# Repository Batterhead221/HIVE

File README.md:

# HIVE

ESP32-C6 gateway board for receiving GRUNT outlet/circuit heartbeat packets.

HIVE is the central receiver in the HIVE + GRUNT monitoring system. It listens for ESP-NOW heartbeat packets from one or more GRUNT sender nodes and reports whether each monitored outlet/circuit is ON, OFF, or waiting for first heartbeat.

## Project Status

Prototype hardware designed. ESP-NOW proof-of-concept tested with an ESP32-C6 gateway and XIAO ESP32-S3 sender node.

## System Role

```text
GRUNT sender node
    ↓ ESP-NOW heartbeat
HIVE gateway board
    ↓ USB serial
Computer / future dashboard
```

## Hardware

Main parts:

- ESP32-C6-WROOM-1-N8 module
- USB-C power and data
- AP2112K-3.3 voltage regulator
- USBLC6-2P6 USB ESD protection
- BOOT and RESET buttons
- RGB status LED
- Power LED
- UART debug pads
- 4-layer PCB with internal GND plane

## Power

HIVE is powered from USB-C VBUS.

```text
USB-C VBUS → fuse/protection → +5V
+5V → AP2112K-3.3 → +3.3V
+3.3V → ESP32-C6-WROOM-1-N8
```

## USB-C

USB-C is used for both power and native ESP32-C6 USB data.

```text
USB D- → ESP32-C6 GPIO12 / USB_D-
USB D+ → ESP32-C6 GPIO13 / USB_D+
CC1 → 5.1k → GND
CC2 → 5.1k → GND
USB shield → GND
```

## Firmware Behavior

HIVE receives heartbeat packets from GRUNT nodes over ESP-NOW.

Each packet contains:

```cpp
typedef struct {
  char nodeId[16];
  uint32_t counter;
  uint32_t uptimeMs;
} HeartbeatPacket;
```

HIVE tracks the last-seen time for each node.

```text
recent heartbeat → node is ON
timeout expired  → node is OFF / missing
never seen       → node is UNKNOWN
```

## PCB Notes

Recommended layer strategy:

```text
T.SIGNAL → components, USB, local signals
GND      → solid internal GND plane
PWR      → +3.3V pour / power routing
B.SIGNAL → GND pour and slow signals
```

Antenna keepout must block copper on all layers:

- No tracks
- No vias
- No pads
- No zone fills
- No components

## Safety Note

HIVE is a low-voltage USB-powered gateway. It does not connect directly to mains voltage.

## Known Notes

- HIVE is the receiver/gateway board.
- GRUNT is the sender/outlet node.
- ESP-NOW devices must be on the same Wi-Fi channel.
- The ESP32-C6 module antenna keepout is critical for reliable wireless performance.
- UART debug pads are included as a backup even though native USB is used.

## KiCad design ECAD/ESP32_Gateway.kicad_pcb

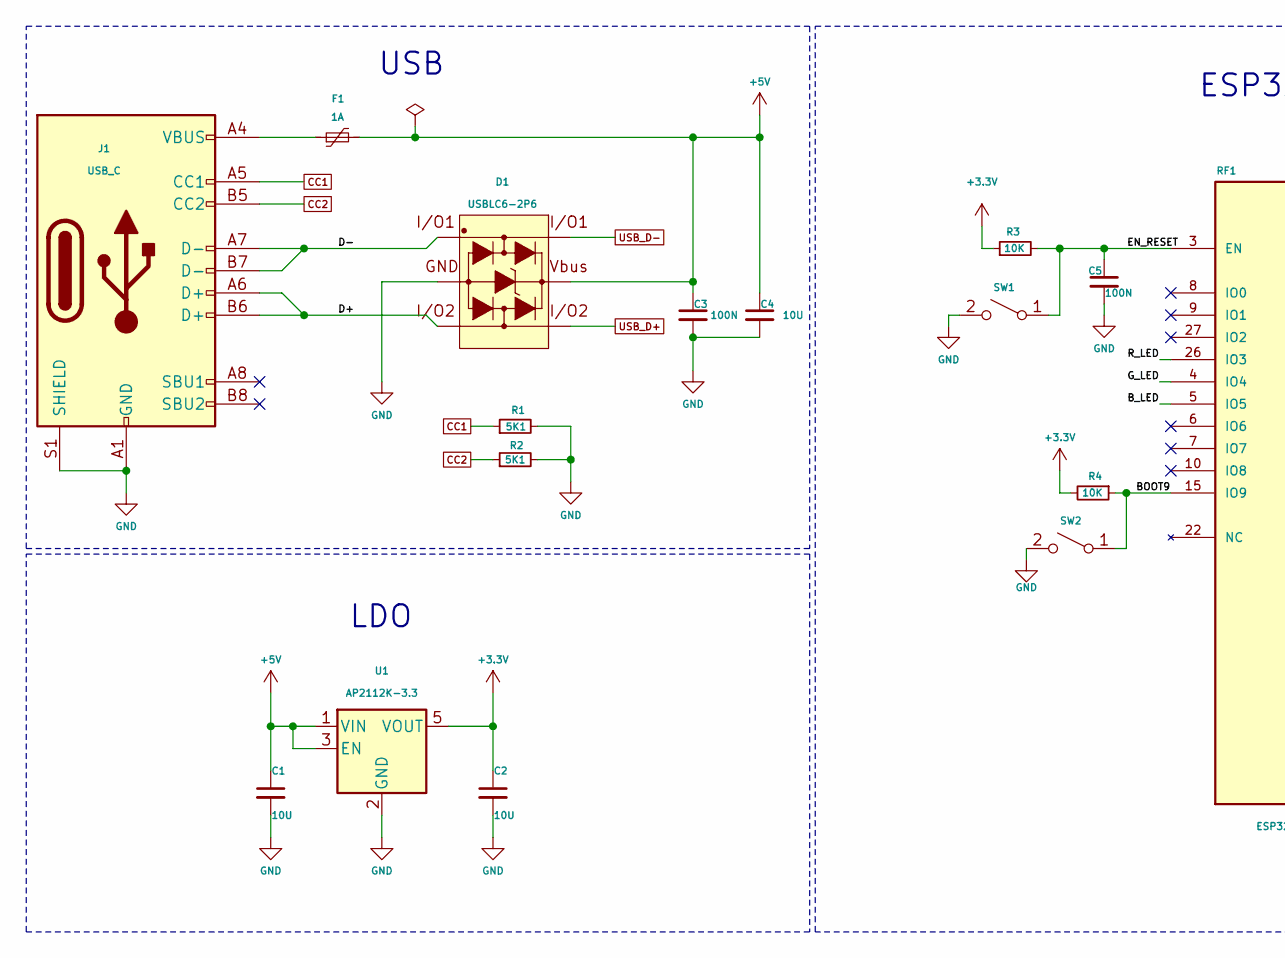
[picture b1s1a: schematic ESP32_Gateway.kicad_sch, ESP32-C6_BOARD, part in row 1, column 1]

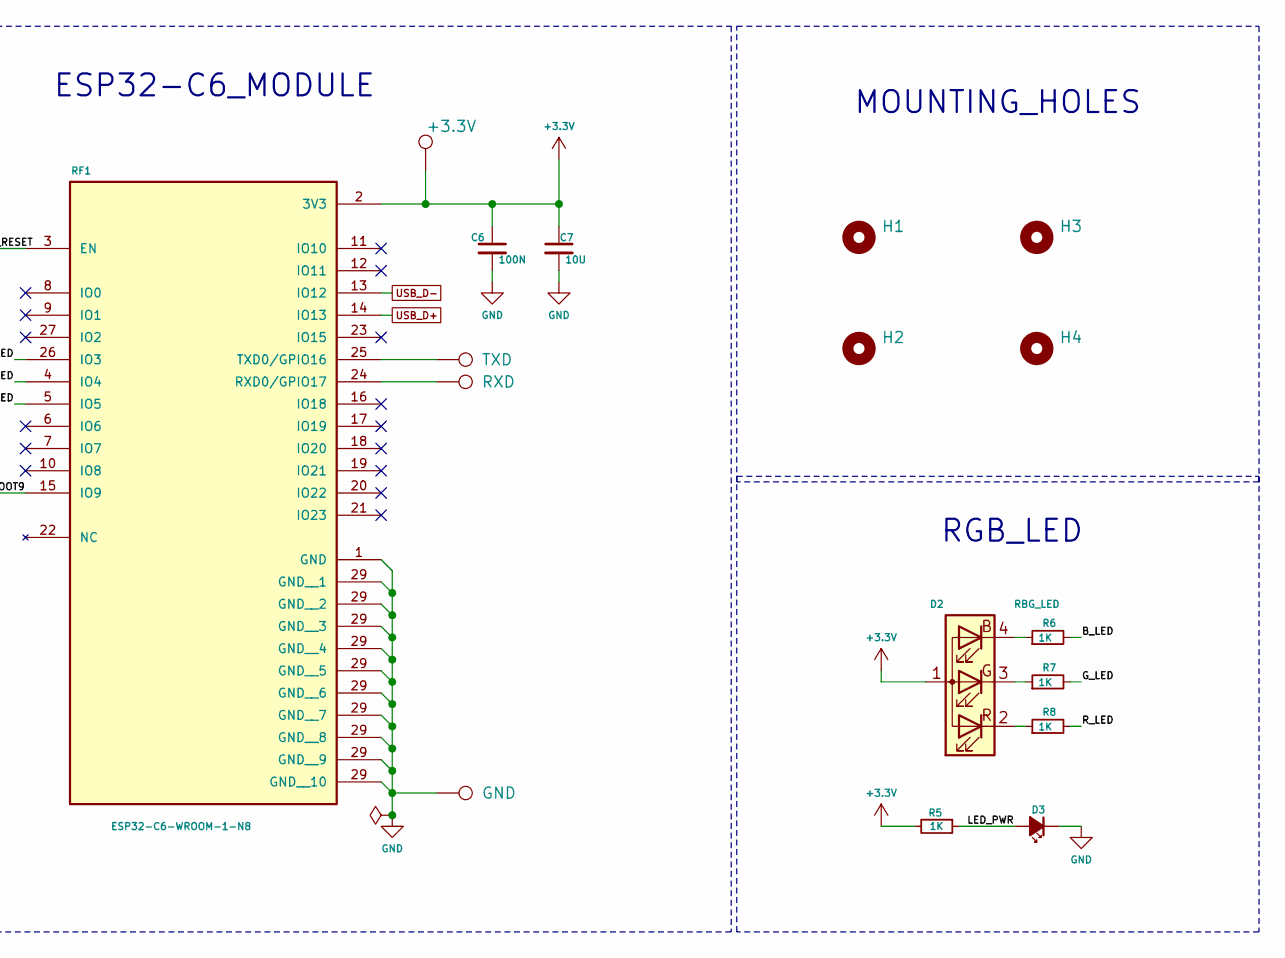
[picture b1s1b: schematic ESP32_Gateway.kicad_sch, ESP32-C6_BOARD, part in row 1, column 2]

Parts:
C1, C2, C4, C7: 10U; C_0805_2012Metric
C3, C5, C6: 100N; C_0603_1608Metric
D1: USBLC6-2P6; SOT-666
D2: RBG_LED; LED_Cree-PLCC4_3.2x2.8mm_CCW
D3: GREEN; LED_0603_1608Metric
F1: 1A; Fuse_1206_3216Metric
H1, H2, H3, H4: MountingHole; MountingHole_2.2mm_M2
J1: USB_C; USB_C_Receptacle_HRO_TYPE-C-31-M-12
R1, R2: 5K1; R_0603
R3, R4: 10K; R_0603
R5, R6, R7, R8: 1K; R_0603
RF1: ESP32-C6-WROOM-1-N8; XCVR_ESP32-C6-WROOM-1-N8; PARTREV 1.0
SW1: RESET; SW_SPST_B3U-1000P
SW2: BOOT; SW_SPST_B3U-1000P
TP1: TXD; TestPoint_THTPad_D1.5mm_Drill0.7mm
TP2: RXD; TestPoint_THTPad_D1.5mm_Drill0.7mm
TP3: GND; TestPoint_THTPad_D1.5mm_Drill0.7mm
TP4: +3.3V; TestPoint_THTPad_D1.5mm_Drill0.7mm
U1: AP2112K-3.3; SOT-23-5

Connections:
+3.3V: C2.1, C6.1, C7.1, D2.1 (A), R3.1, R4.2, R5.2, RF1.2 (3V3), TP4.1 (1_1), U1.5 (VOUT)
+5V: C1.1, C3.1, C4.1, D1.5 (Vbus), F1.2, U1.1 (VIN), U1.3 (EN)
/BOOT9: R4.1, RF1.15 (IO9), SW2.1 (A)
/B_LED: R6.2, RF1.5 (IO5)
/D+: D1.3 (I/O2), J1.A6 (D+), J1.B6 (D+)
/D-: D1.1 (I/O1), J1.A7 (D-), J1.B7 (D-)
/EN_RESET: C5.1, R3.2, RF1.3 (EN), SW1.1 (A)
/G_LED: R7.2, RF1.4 (IO4)
/LED_PWR: D3.2 (A), R5.1
/R_LED: R8.2, RF1.26 (IO3)
CC1: J1.A5 (CC1), R1.1
CC2: J1.B5 (CC2), R2.1
GND: C1.2, C2.2, C3.2, C4.2, C5.2, C6.2, C7.2, D1.2 (GND), D3.1 (K), J1.A1 (GND), J1.A12 (GND), J1.B1 (GND), J1.B12 (GND), J1.S1 (SHIELD), R1.2, R2.2, RF1.1 (GND), RF1.29 (GND__1), SW1.2 (B), SW2.2 (B), TP3.1 (1_1), U1.2 (GND)
unnamed: D2.4 (BK), R6.1
unnamed: D2.3 (GK), R7.1
unnamed: D2.2 (RK), R8.1
unnamed: F1.1, J1.A4 (VBUS), J1.A9 (VBUS), J1.B4 (VBUS), J1.B9 (VBUS)
unnamed: RF1.24 (RXD0/GPIO17), TP2.1 (1_1)
unnamed: RF1.25 (TXD0/GPIO16), TP1.1 (1_1)
USB_D+: D1.4 (I/O2+), RF1.14 (IO13)
USB_D-: D1.6 (I/O1+), RF1.13 (IO12)

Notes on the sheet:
LDO
MOUNTING_HOLES
RGB_LED
ESP32-C6_MODULE
USB

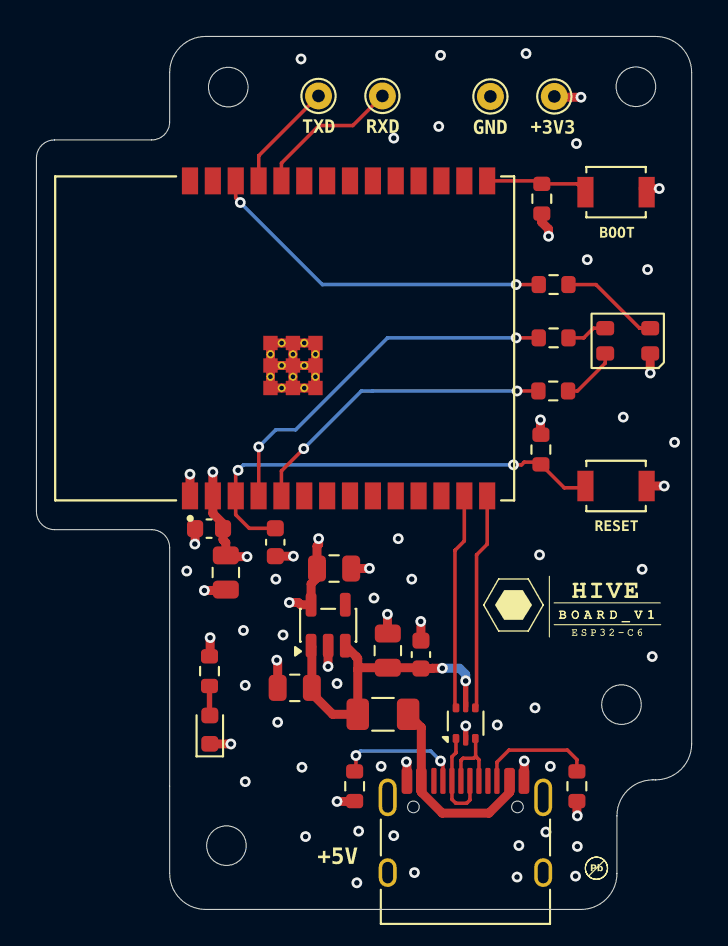
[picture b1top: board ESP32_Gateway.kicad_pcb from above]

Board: 4 copper layers, 36.4 x 48.5 mm, 32 parts (0 on the bottom side), 21 nets.

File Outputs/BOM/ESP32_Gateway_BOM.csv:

"Id";"Designator";"Footprint";"Quantity";"Designation";"Supplier and ref";
1;"C1, C2, C4, C7";"C_0805_2012Metric";4;"10U";;;
2;"C3, C5, C6";"C_0603_1608Metric";3;"100N";;;
3;"D1";"SOT-666";1;"USBLC6-2P6";;;
4;"D2";"LED_Cree-PLCC4_3.2x2.8mm_CCW";1;"RBG_LED";;;
5;"D3";"LED_0603_1608Metric";1;"GREEN";;;
6;"F1";"Fuse_1206_3216Metric";1;"1A";;;
7;"J1";"USB_C_Receptacle_HRO_TYPE-C-31-M-12";1;"USB_C";;;
8;"R1, R2";"R_0603";2;"5K1";;;
9;"R3, R4";"R_0603";2;"10K";;;
10;"R5, R6, R7, R8";"R_0603";4;"1K";;;
11;"RF1";"XCVR_ESP32-C6-WROOM-1-N8";1;"ESP32-C6-WROOM-1-N8";;;
12;"SW1";"SW_SPST_B3U-1000P";1;"RESET";;;
13;"SW2";"SW_SPST_B3U-1000P";1;"BOOT";;;
14;"TP1";"TestPoint_THTPad_D1.5mm_Drill0.7mm";1;"TXD";;;
15;"TP2";"TestPoint_THTPad_D1.5mm_Drill0.7mm";1;"RXD";;;
16;"TP3";"TestPoint_THTPad_D1.5mm_Drill0.7mm";1;"GND";;;
17;"TP4";"TestPoint_THTPad_D1.5mm_Drill0.7mm";1;"+3.3V";;;
18;"U1";"SOT-23-5";1;"AP2112K-3.3";;;

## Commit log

2026-05-23 update repo
2026-05-23 moved old firmware
